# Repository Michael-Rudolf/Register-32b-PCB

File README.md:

# Register-32b-PCB
A PCB that stores 32b and has 5-bit addressing.

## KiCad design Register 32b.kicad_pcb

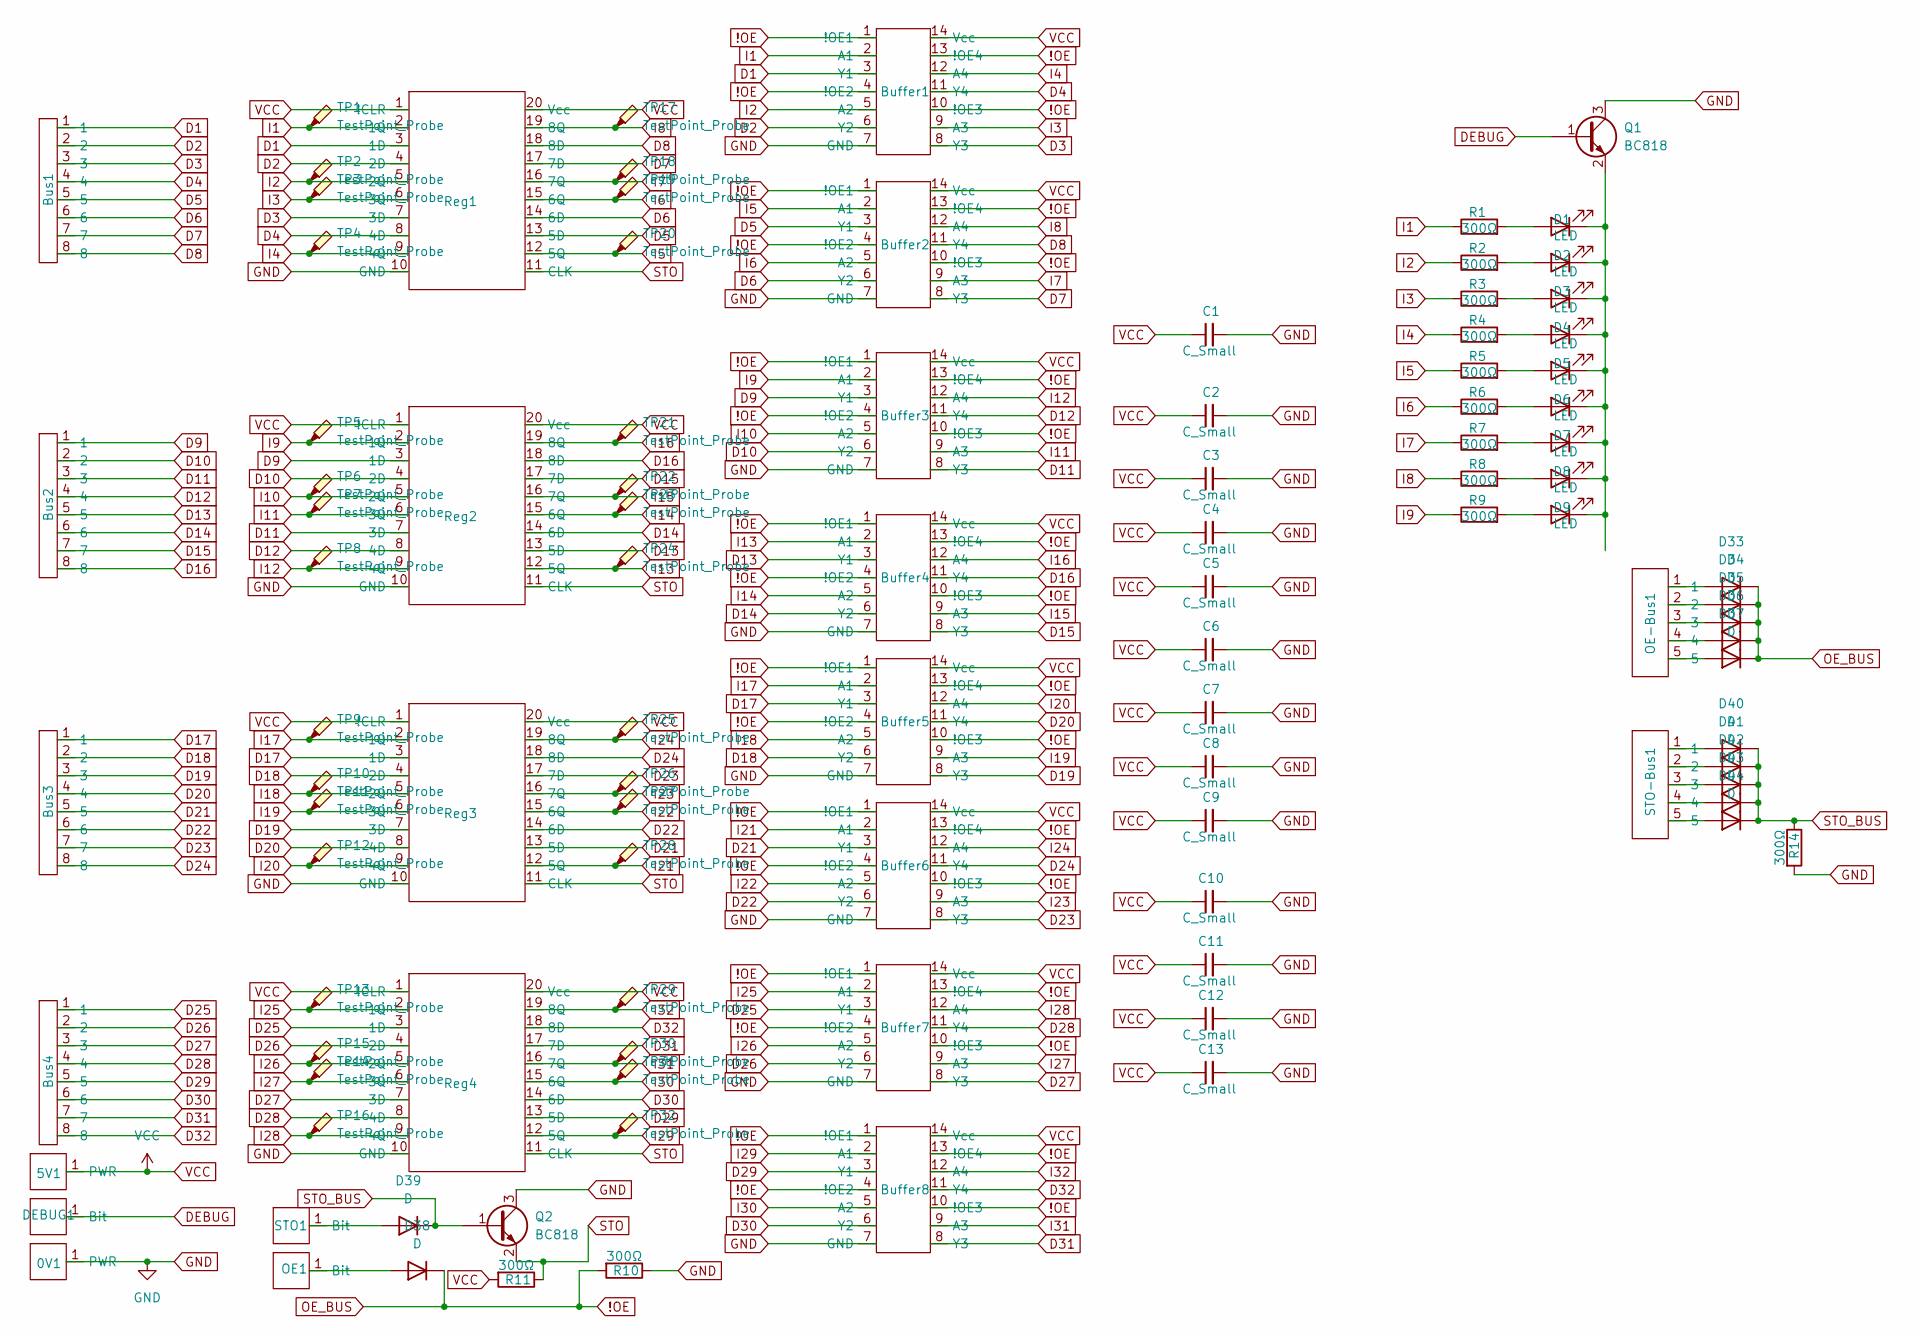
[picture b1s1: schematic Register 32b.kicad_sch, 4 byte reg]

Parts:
0V1, 5V1: Single Bit Mini Bus
Buffer1, Buffer2, Buffer3, Buffer4, Buffer5, Buffer6, Buffer7, Buffer8: SNx4HCT125
Bus1, Bus2, Bus3, Bus4: 8 Bit Bus Small
C1, C2, C3, C4, C5, C6, C7, C8, C9, C10, C11, C12, C13: C_Small; C_0805_2012Metric_Pad1.18x1.45mm_HandSolder
D1, D2, D3, D4, D5, D6, D7, D8, D9: LED; LED_0805_2012Metric_Pad1.15x1.40mm_HandSolder
D33, D34, D35, D36, D37, D38, D39, D40, D41, D42, D43, D44: D; D_0805_2012Metric_Pad1.15x1.40mm_HandSolder
DEBUG1: Single Bit Mini Bus
OE1: Single Bit Mini Bus
OE-Bus1: 5 Bit Bus With Passing Holes
Q1, Q2: BC818; SOT-23
R1, R2, R3, R4, R5, R6, R7, R8, R9, R10, R11, R14: 300Ω; R_0805_2012Metric_Pad1.20x1.40mm_HandSolder
Reg1, Reg2, Reg3, Reg4: SN74HC273 TSSOP
STO1: Single Bit Mini Bus
STO-Bus1: 5 Bit Bus With Passing Holes
TP1, TP2, TP3, TP4, TP5, TP6, TP7, TP8, TP9, TP10, TP11, TP12, TP13, TP14, TP15, TP16, TP17, TP18, TP19, TP20, TP21, TP22, TP23, TP24, TP25, TP26, TP27, TP28, TP29, TP30, TP31, TP32: TestPoint_Probe; TestPoint_Pad_1.0x1.0mm

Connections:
!OE: Buffer1.1 (!OE1), Buffer1.4 (!OE2), Buffer1.10 (!OE3), Buffer1.13 (!OE4), Buffer2.1 (!OE1), Buffer2.4 (!OE2), Buffer2.10 (!OE3), Buffer2.13 (!OE4), Buffer3.1 (!OE1), Buffer3.4 (!OE2), Buffer3.10 (!OE3), Buffer3.13 (!OE4), Buffer4.1 (!OE1), Buffer4.4 (!OE2), Buffer4.10 (!OE3), Buffer4.13 (!OE4), Buffer5.1 (!OE1), Buffer5.4 (!OE2), Buffer5.10 (!OE3), Buffer5.13 (!OE4), Buffer6.1 (!OE1), Buffer6.4 (!OE2), Buffer6.10 (!OE3), Buffer6.13 (!OE4), Buffer7.1 (!OE1), Buffer7.4 (!OE2), Buffer7.10 (!OE3), Buffer7.13 (!OE4), Buffer8.1 (!OE1), Buffer8.4 (!OE2), Buffer8.10 (!OE3), Buffer8.13 (!OE4), D33.1 (K), D34.1 (K), D35.1 (K), D36.1 (K), D37.1 (K), D38.1 (K), R10.2
D1: Buffer1.3 (Y1), Bus1.1, Reg1.3 (1D)
D2: Buffer1.6 (Y2), Bus1.2, Reg1.4 (2D)
D3: Buffer1.8 (Y3), Bus1.3, Reg1.7 (3D)
D4: Buffer1.11 (Y4), Bus1.4, Reg1.8 (4D)
D5: Buffer2.3 (Y1), Bus1.5, Reg1.13 (5D)
D6: Buffer2.6 (Y2), Bus1.6, Reg1.14 (6D)
D7: Buffer2.8 (Y3), Bus1.7, Reg1.17 (7D)
D8: Buffer2.11 (Y4), Bus1.8, Reg1.18 (8D)
D9: Buffer3.3 (Y1), Bus2.1, Reg2.3 (1D)
D10: Buffer3.6 (Y2), Bus2.2, Reg2.4 (2D)
D11: Buffer3.8 (Y3), Bus2.3, Reg2.7 (3D)
D12: Buffer3.11 (Y4), Bus2.4, Reg2.8 (4D)
D13: Buffer4.3 (Y1), Bus2.5, Reg2.13 (5D)
D14: Buffer4.6 (Y2), Bus2.6, Reg2.14 (6D)
D15: Buffer4.8 (Y3), Bus2.7, Reg2.17 (7D)
D16: Buffer4.11 (Y4), Bus2.8, Reg2.18 (8D)
D17: Buffer5.3 (Y1), Bus3.1, Reg3.3 (1D)
D18: Buffer5.6 (Y2), Bus3.2, Reg3.4 (2D)
D19: Buffer5.8 (Y3), Bus3.3, Reg3.7 (3D)
D20: Buffer5.11 (Y4), Bus3.4, Reg3.8 (4D)
D21: Buffer6.3 (Y1), Bus3.5, Reg3.13 (5D)
D22: Buffer6.6 (Y2), Bus3.6, Reg3.14 (6D)
D23: Buffer6.8 (Y3), Bus3.7, Reg3.17 (7D)
D24: Buffer6.11 (Y4), Bus3.8, Reg3.18 (8D)
D25: Buffer7.3 (Y1), Bus4.1, Reg4.3 (1D)
D26: Buffer7.6 (Y2), Bus4.2, Reg4.4 (2D)
D27: Buffer7.8 (Y3), Bus4.3, Reg4.7 (3D)
D28: Buffer7.11 (Y4), Bus4.4, Reg4.8 (4D)
D29: Buffer8.3 (Y1), Bus4.5, Reg4.13 (5D)
D30: Buffer8.6 (Y2), Bus4.6, Reg4.14 (6D)
D31: Buffer8.8 (Y3), Bus4.7, Reg4.17 (7D)
D32: Buffer8.11 (Y4), Bus4.8, Reg4.18 (8D)
DEBUG: DEBUG1.1 (Bit), Q1.1 (B)
GND: 0V1.1 (PWR), Buffer1.7 (GND), Buffer2.7 (GND), Buffer3.7 (GND), Buffer4.7 (GND), Buffer5.7 (GND), Buffer6.7 (GND), Buffer7.7 (GND), Buffer8.7 (GND), C1.2, C2.2, C3.2, C4.2, C5.2, C6.2, C7.2, C8.2, C9.2, C10.2, C11.2, C12.2, C13.2, Q1.3 (C), Q2.3 (C), R10.1, R14.2, Reg1.10 (GND), Reg2.10 (GND), Reg3.10 (GND), Reg4.10 (GND)
I1: Buffer1.2 (A1), R1.1, Reg1.2 (1Q), TP1.1
I2: Buffer1.5 (A2), R2.1, Reg1.5 (2Q), TP2.1
I3: Buffer1.9 (A3), R3.1, Reg1.6 (3Q), TP3.1
I4: Buffer1.12 (A4), R4.1, Reg1.9 (4Q), TP4.1
I5: Buffer2.2 (A1), R5.1, Reg1.12 (5Q), TP20.1
I6: Buffer2.5 (A2), R6.1, Reg1.15 (6Q), TP19.1
I7: Buffer2.9 (A3), R7.1, Reg1.16 (7Q), TP18.1
I8: Buffer2.12 (A4), R8.1, Reg1.19 (8Q), TP17.1
I9: Buffer3.2 (A1), R9.1, Reg2.2 (1Q), TP5.1
I10: Buffer3.5 (A2), Reg2.5 (2Q), TP6.1
I11: Buffer3.9 (A3), Reg2.6 (3Q), TP7.1
I12: Buffer3.12 (A4), Reg2.9 (4Q), TP8.1
I13: Buffer4.2 (A1), Reg2.12 (5Q), TP24.1
I14: Buffer4.5 (A2), Reg2.15 (6Q), TP23.1
I15: Buffer4.9 (A3), Reg2.16 (7Q), TP22.1
I16: Buffer4.12 (A4), Reg2.19 (8Q), TP21.1
I17: Buffer5.2 (A1), Reg3.2 (1Q), TP9.1
I18: Buffer5.5 (A2), Reg3.5 (2Q), TP10.1
I19: Buffer5.9 (A3), Reg3.6 (3Q), TP11.1
I20: Buffer5.12 (A4), Reg3.9 (4Q), TP12.1
I21: Buffer6.2 (A1), Reg3.12 (5Q), TP28.1
I22: Buffer6.5 (A2), Reg3.15 (6Q), TP27.1
I23: Buffer6.9 (A3), Reg3.16 (7Q), TP26.1
I24: Buffer6.12 (A4), Reg3.19 (8Q), TP25.1
I25: Buffer7.2 (A1), Reg4.2 (1Q), TP13.1
I26: Buffer7.5 (A2), Reg4.5 (2Q), TP15.1
I27: Buffer7.9 (A3), Reg4.6 (3Q), TP14.1
I28: Buffer7.12 (A4), Reg4.9 (4Q), TP16.1
I29: Buffer8.2 (A1), Reg4.12 (5Q), TP32.1
I30: Buffer8.5 (A2), Reg4.15 (6Q), TP31.1
I31: Buffer8.9 (A3), Reg4.16 (7Q), TP30.1
I32: Buffer8.12 (A4), Reg4.19 (8Q), TP29.1
unnamed: D1.2 (A), R1.2
unnamed: D1.1 (K), D2.1 (K), D3.1 (K), D4.1 (K), D5.1 (K), D6.1 (K), D7.1 (K), D8.1 (K), D9.1 (K), Q1.2 (E)
unnamed: D2.2 (A), R2.2
unnamed: D3.2 (A), R3.2
unnamed: D4.2 (A), R4.2
unnamed: D5.2 (A), R5.2
unnamed: D6.2 (A), R6.2
unnamed: D7.2 (A), R7.2
unnamed: D8.2 (A), R8.2
unnamed: D9.2 (A), R9.2
unnamed: D33.2 (A), OE-Bus1.1
unnamed: D34.2 (A), OE-Bus1.2
unnamed: D35.2 (A), OE-Bus1.3
unnamed: D36.2 (A), OE-Bus1.4
unnamed: D37.2 (A), OE-Bus1.5
unnamed: D38.2 (A), OE1.1 (Bit)
unnamed: D39.2 (A), STO1.1 (Bit)
unnamed: D40.2 (A), STO-Bus1.1
unnamed: D41.2 (A), STO-Bus1.2
unnamed: D42.2 (A), STO-Bus1.3
unnamed: D43.2 (A), STO-Bus1.4
unnamed: D44.2 (A), STO-Bus1.5
STO: Q2.2 (E), R11.1, Reg1.11 (CLK), Reg2.11 (CLK), Reg3.11 (CLK), Reg4.11 (CLK)
STO_BUS: D39.1 (K), D40.1 (K), D41.1 (K), D42.1 (K), D43.1 (K), D44.1 (K), Q2.1 (B), R14.1
VCC: 5V1.1 (PWR), Buffer1.14 (Vcc), Buffer2.14 (Vcc), Buffer3.14 (Vcc), Buffer4.14 (Vcc), Buffer5.14 (Vcc), Buffer6.14 (Vcc), Buffer7.14 (Vcc), Buffer8.14 (Vcc), C1.1, C2.1, C3.1, C4.1, C5.1, C6.1, C7.1, C8.1, C9.1, C10.1, C11.1, C12.1, C13.1, R11.2, Reg1.1 (!CLR), Reg1.20 (Vcc), Reg2.1 (!CLR), Reg2.20 (Vcc), Reg3.1 (!CLR), Reg3.20 (Vcc), Reg4.1 (!CLR), Reg4.20 (Vcc)

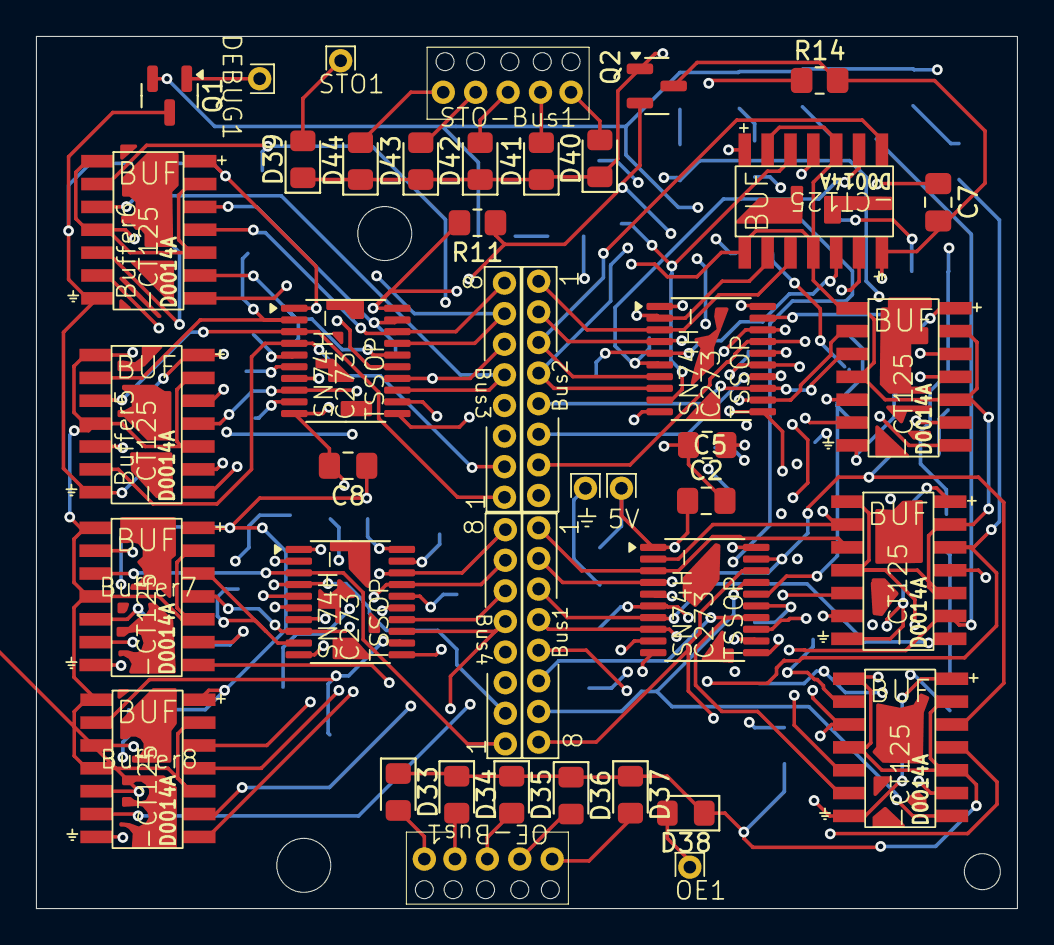
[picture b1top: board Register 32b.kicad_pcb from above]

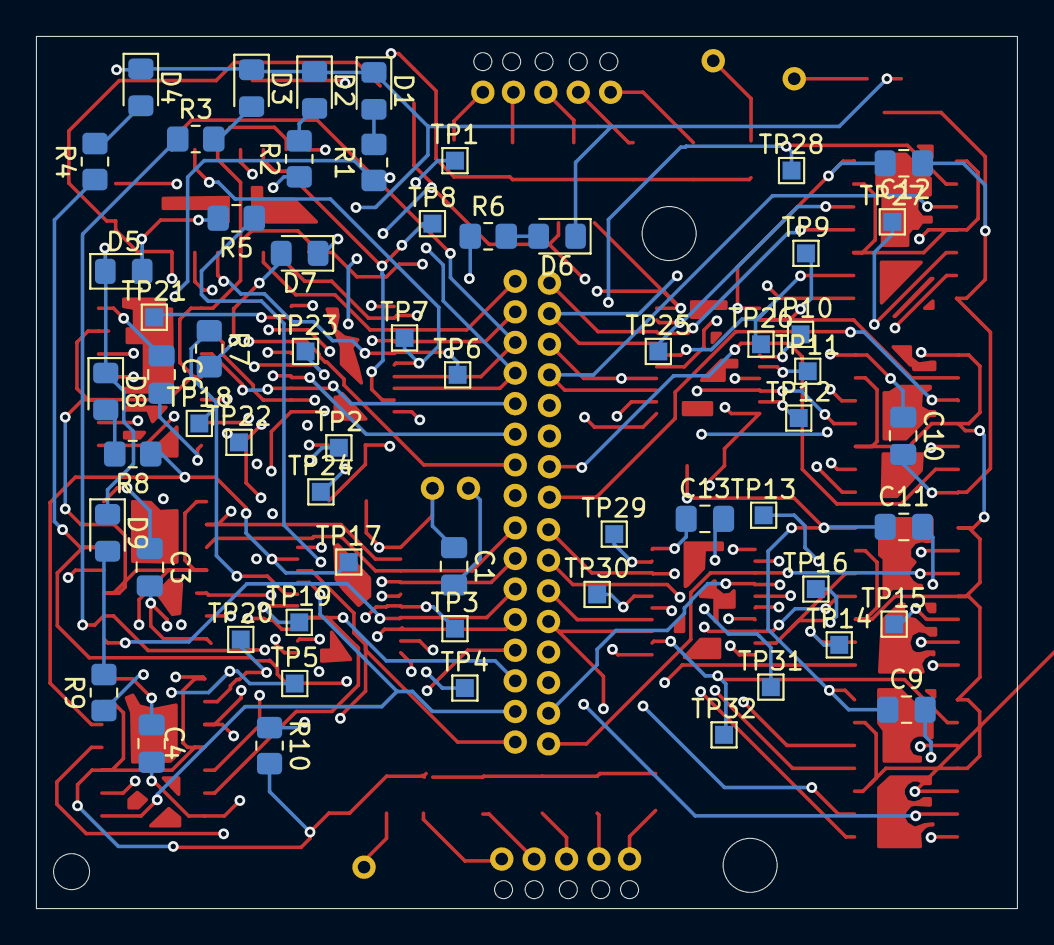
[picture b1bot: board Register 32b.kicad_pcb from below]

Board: 4 copper layers, 54.5 x 48.5 mm, 103 parts (60 on the bottom side), 92 nets.

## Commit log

2025-06-16 Gitignore file added
2025-06-16 Uploaded projects files
